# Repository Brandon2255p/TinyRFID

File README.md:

# TinyRFID
The full project for the TinyRFID PCB design and source code

To Checkout:

```
git clone --recursive https://github.com/Brandon2255p/TinyRFID.git
```

## Firmware

`Firmware/` is a [PlatformIO](https://platformio.org/) project for an ESP32
EM4100 (125 kHz) tag emulator with a browser-based web interface. It supports
a half-bit **sweep** (200–220 µs) or a specific fixed rate per card, and stores
card IDs in the browser. See [`Firmware/README.md`](Firmware/README.md).

```bash
cd Firmware
pio run -t upload
```

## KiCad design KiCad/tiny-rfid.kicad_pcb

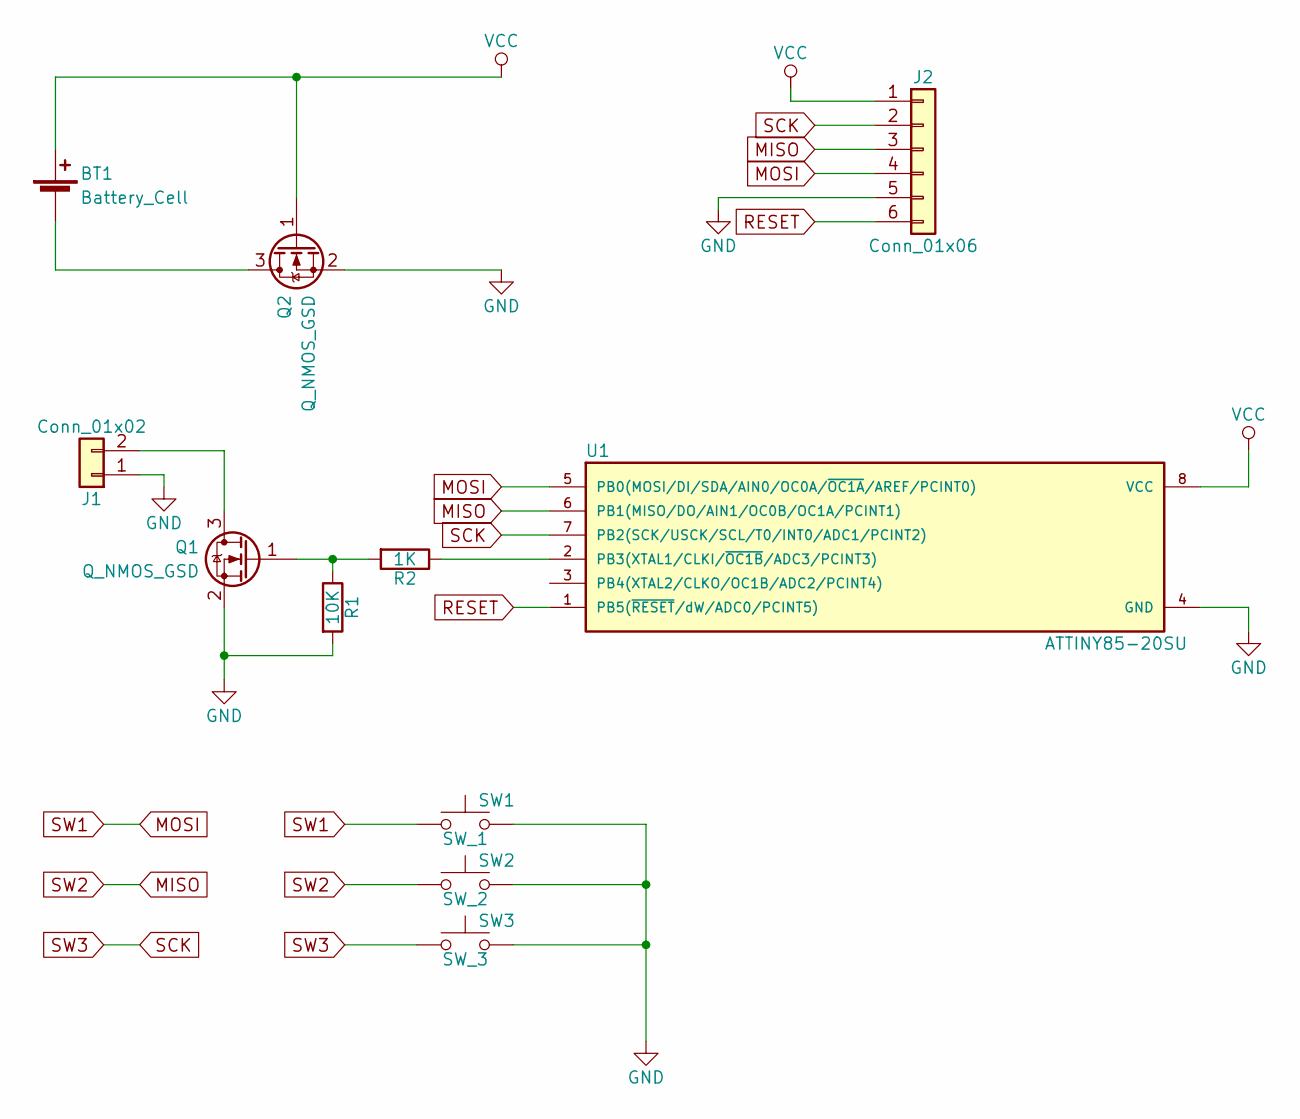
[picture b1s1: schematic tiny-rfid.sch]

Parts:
BT1: Battery_Cell; Embedded_CR2032
J1: Conn_01x02; Pin_Header_Straight_1x02_Pitch1.27mm
J2: Conn_01x06; Pin_Header_Straight_1x06_Pitch2.00mm
Q1, Q2: Q_NMOS_GSD; SOT-23
R1: 10K; R_0805_HandSoldering
R2: 1K; R_0805_HandSoldering
SW1: SW_1; SW_SPST_B3S-1000
SW2: SW_2; SW_SPST_B3S-1000
SW3: SW_3; SW_SPST_B3S-1000
U1: ATTINY85-20SU; SOIC-8_3.9x4.9mm_Pitch1.27mm

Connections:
GND: J1.1, J2.5, Q1.2 (S), Q2.2 (S), R1.2, SW1.2, SW2.2, SW3.2, U1.4 (GND)
MISO: J2.3, SW2.1, U1.6 (PB1(MISO/DO/AIN1/OC0B/OC1A/PCINT1))
MOSI: J2.4, SW1.1, U1.5 (PB0(MOSI/DI/SDA/AIN0/OC0A/~OC1A~/AREF/P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)
unnamed: BT1.2 (-), Q2.3 (D)
unnamed: J1.2, Q1.3 (D)
unnamed: Q1.1 (G), R1.1, R2.2
unnamed: R2.1, U1.2 (PB3(XTAL1/CLKI/~OC1B~/ADC3/PCINT3))
RESET: J2.6, U1.1 (PB5(~RESET~/dW/ADC0/PCINT5))
SCK: J2.2, SW3.1, U1.7 (PB2(SCK/USCK/SCL/T0/INT0/ADC1/PCINT2))
VCC: BT1.1 (+), J2.1, Q2.1 (G), U1.8 (VCC)

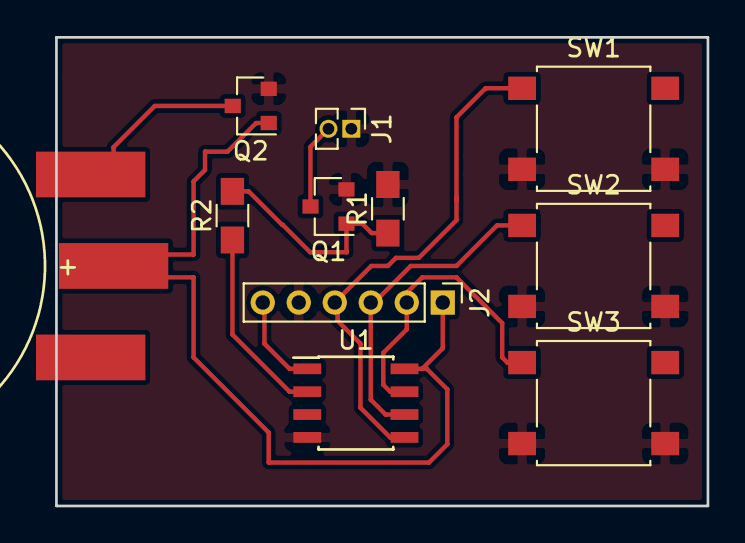
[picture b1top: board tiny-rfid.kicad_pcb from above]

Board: 2 copper layers, 36.2 x 26.0 mm, 11 parts (0 on the bottom side), 10 nets.

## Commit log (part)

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2017-12-12 Added initial KiCad design files
2017-12-12 Added submodule dependencies
2017-12-12 Updated KiCadLib with a footprint required in this project
2017-12-12 Changed 3d model for button
2017-12-12 Update readme
    Added how to checkout
